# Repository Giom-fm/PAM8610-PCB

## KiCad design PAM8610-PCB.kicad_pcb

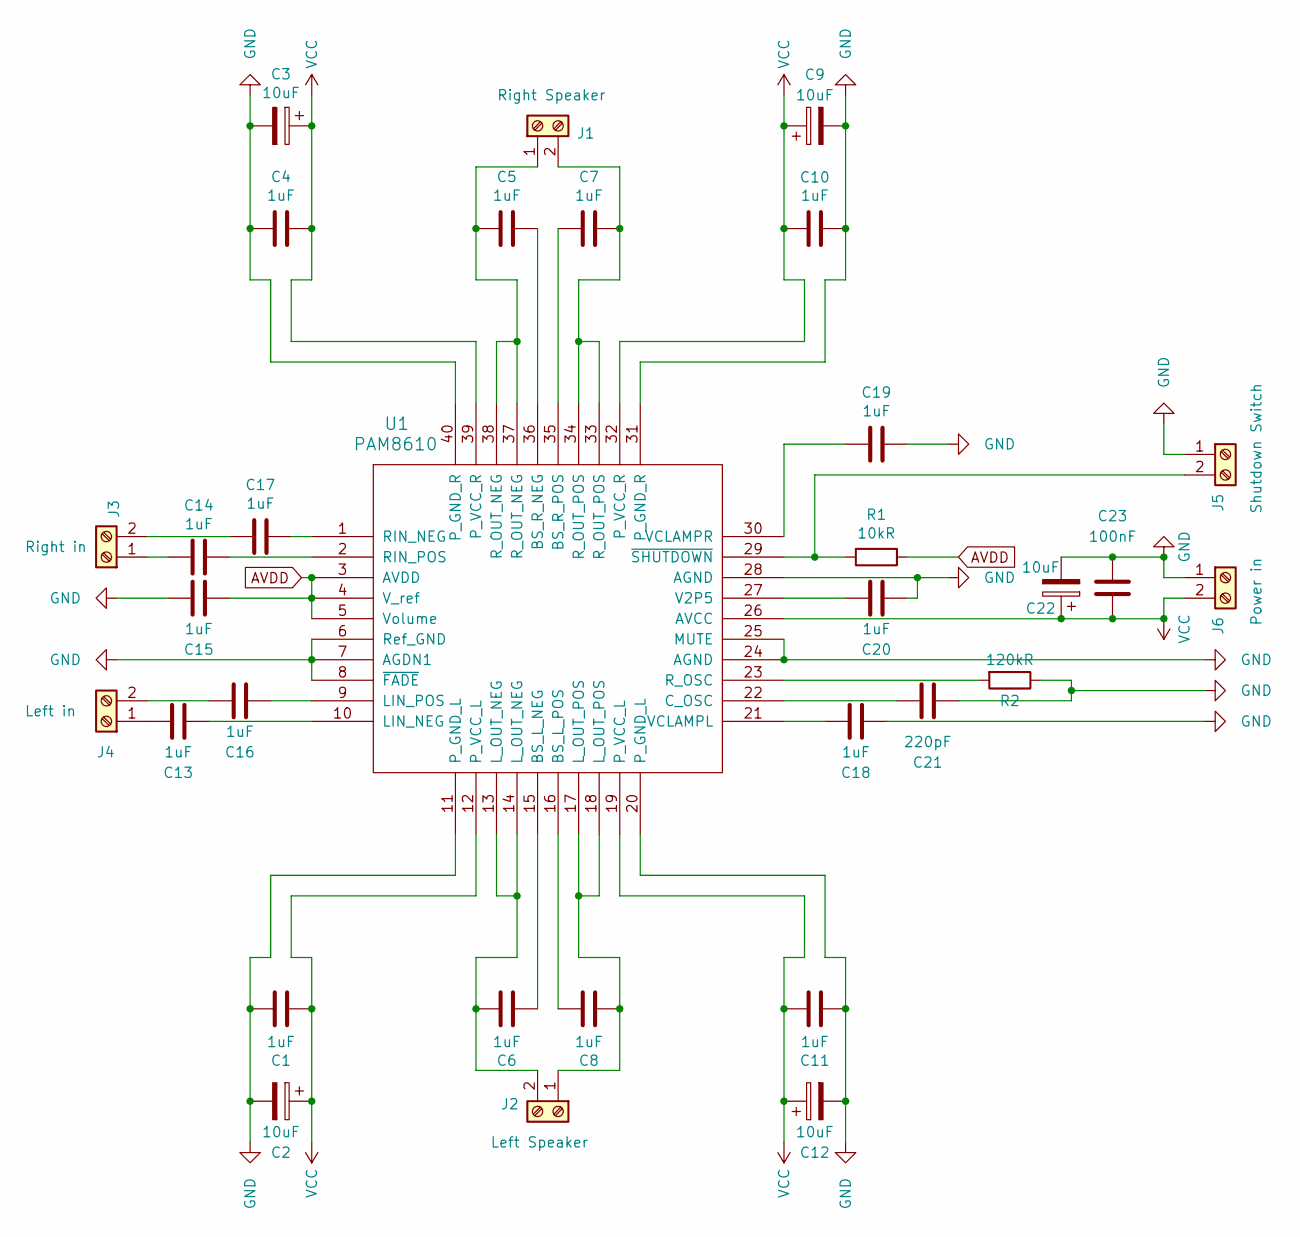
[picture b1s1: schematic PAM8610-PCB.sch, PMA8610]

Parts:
C1, C4, C5, C6, C7, C8, C10, C11, C13, C14, C15, C16, C17, C18, C19, C20: 1uF; C_0805_2012Metric
C2, C3, C9, C12, C22: 10uF; CP_Radial_D4.0mm_P1.50mm
C21: 220pF; C_0805_2012Metric
C23: 100nF; C_0805_2012Metric
J1: Right Speaker; PinHeader_1x02_P2.54mm_Vertical
J2: Left Speaker; PinHeader_1x02_P2.54mm_Vertical
J3: Right in; PinHeader_1x02_P2.54mm_Vertical
J4: Left in; PinHeader_1x02_P2.54mm_Vertical
J5: Shutdown Switch; PinHeader_1x02_P2.54mm_Vertical
J6: Power in; PinHeader_1x02_P2.54mm_Vertical
R1: 10kR; R_0805_2012Metric
R2: 120kR; R_0805_2012Metric
U1: PAM8610; QFN-40-1EP_6x6mm_P0.5mm_EP4.6x4.6mm_ThermalVias

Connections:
AVDD: C15.1, R1.1, U1.3 (AVDD), U1.4 (V_ref), U1.5 (Volume)
GND: C1.1, C2.2, C3.2, C4.2, C9.2, C10.1, C11.2, C12.2, C15.2, C18.2, C19.1, C20.2, C21.2, C22.2, C23.2, J5.1, J6.1, R2.1, U1.6 (Ref_GND), U1.7 (AGDN1), U1.8 (~FADE), U1.11 (P_GND_L), U1.20 (P_GND_L), U1.24 (AGND), U1.25 (MUTE), U1.28 (AGND), U1.31 (P_GND_R), U1.40 (P_GND_R)
unnamed: C5.1, U1.36 (BS_R_NEG)
unnamed: C5.2, J1.1, U1.37 (R_OUT_NEG), U1.38 (R_OUT_NEG)
unnamed: C6.1, J2.2, U1.13 (L_OUT_NEG), U1.14 (L_OUT_NEG)
unnamed: C6.2, U1.15 (BS_L_NEG)
unnamed: C7.1, J1.2, U1.33 (R_OUT_POS), U1.34 (R_OUT_POS)
unnamed: C7.2, U1.35 (BS_R_POS)
unnamed: C8.1, U1.16 (BS_L_POS)
unnamed: C8.2, J2.1, U1.17 (L_OUT_POS), U1.18 (L_OUT_POS)
unnamed: C13.1, U1.10 (LIN_NEG)
unnamed: C13.2, J4.1
unnamed: C14.1, U1.2 (RIN_POS)
unnamed: C14.2, J3.1
unnamed: C16.1, U1.9 (LIN_POS)
unnamed: C16.2, J4.2
unnamed: C17.1, U1.1 (RIN_NEG)
unnamed: C17.2, J3.2
unnamed: C18.1, U1.21 (VCLAMPL)
unnamed: C19.2, U1.30 (VCLAMPR)
unnamed: C20.1, U1.27 (V2P5)
unnamed: C21.1, U1.22 (C_OSC)
unnamed: J5.2, R1.2, U1.29 (~SHUTDOWN)
unnamed: R2.2, U1.23 (R_OSC)
VCC: C1.2, C2.1, C3.1, C4.1, C9.1, C10.2, C11.1, C12.1, C22.1, C23.1, J6.2, U1.12 (P_VCC_L), U1.19 (P_VCC_L), U1.26 (AVCC), U1.32 (P_VCC_R), U1.39 (P_VCC_R)

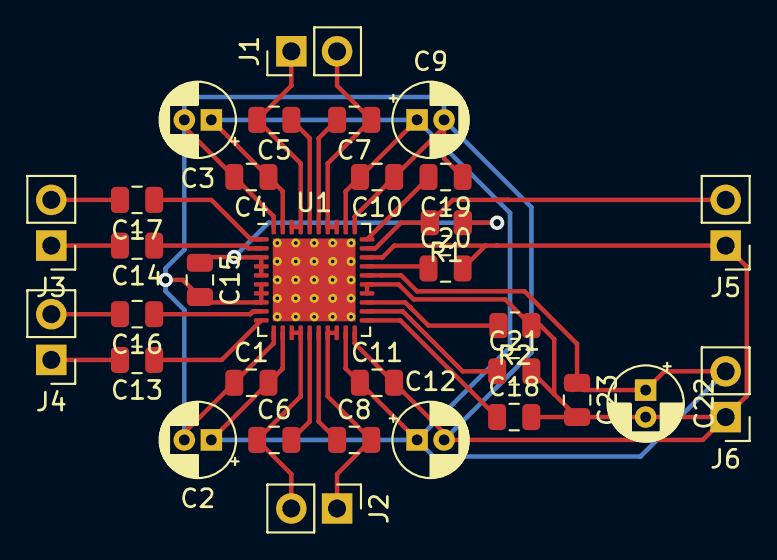
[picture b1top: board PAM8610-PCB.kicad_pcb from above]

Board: 2 copper layers, 32 parts (0 on the bottom side), 25 nets.

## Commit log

2020-11-07 init
2020-11-07 add Readme
